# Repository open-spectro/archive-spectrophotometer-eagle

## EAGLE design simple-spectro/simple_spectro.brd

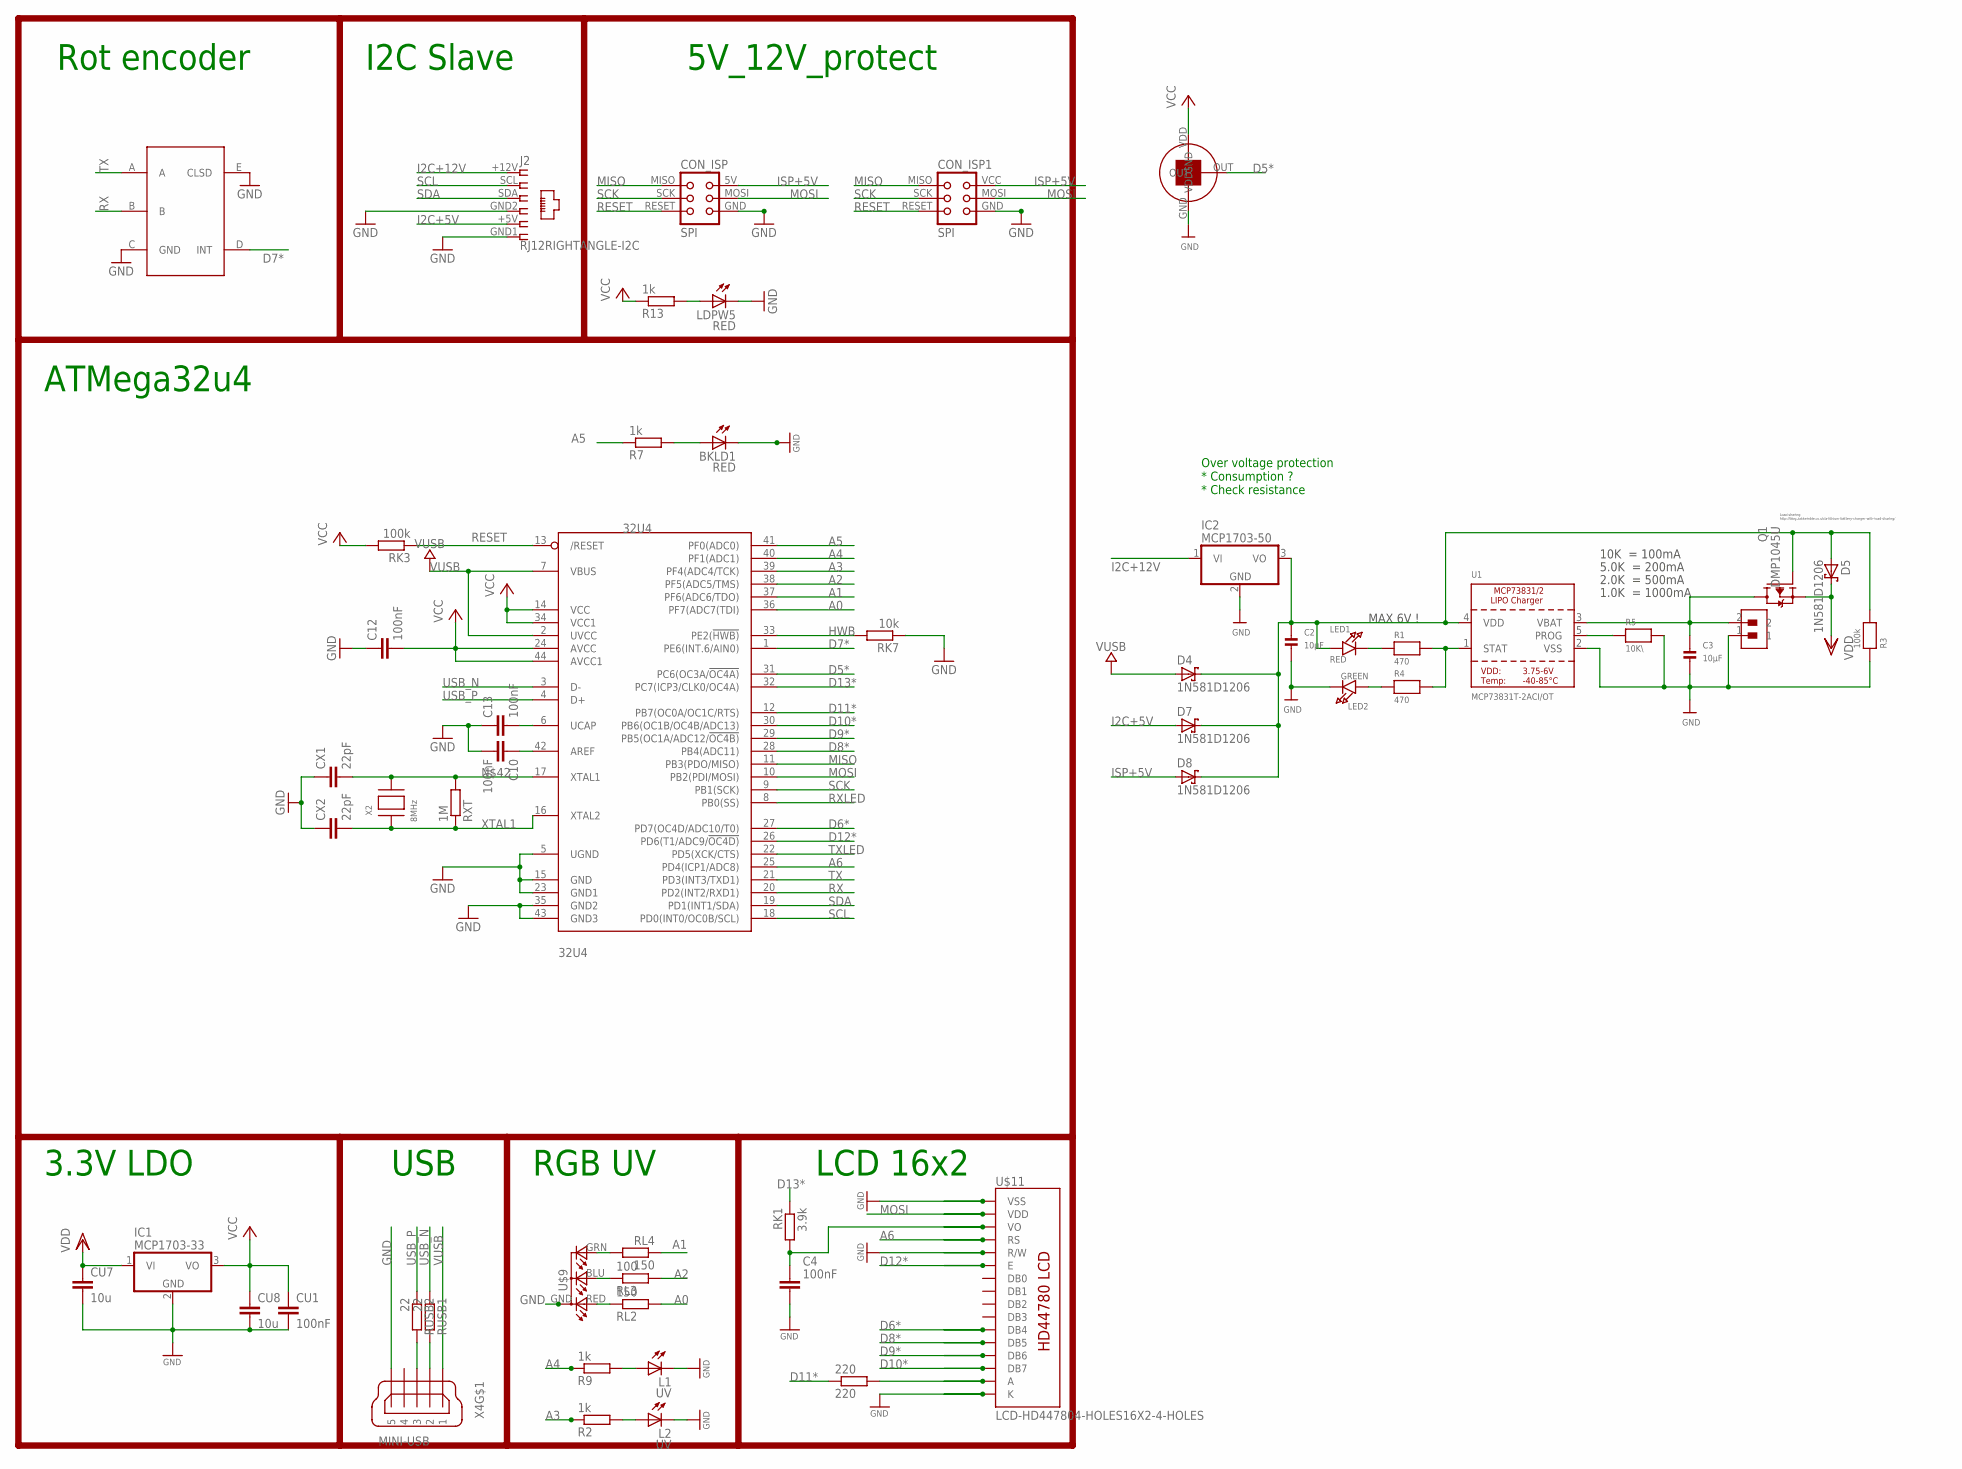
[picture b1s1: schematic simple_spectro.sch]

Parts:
32U4: 32U4; TQFP44
220: 220; R0805
BKLD1: RED; CHIP-LED0805
C2, C3: 10µF; 0805
C4: 100nF; C805
C10, C12, C13: 100nF; C1206
CON_ISP: SPI; TC2030-MCP-NL
CON_ISP1: SPI; TINYISP
CU1: 100nF; C0805
CU7, CU8: 10u; C0805
CX1, CX2: 22pF; C1206
D4, D5, D7, D8: 1N581D1206; LED-1206
IC1: MCP1703-33; SOT223
IC2: MCP1703-50; SOT223
J2: RJ12RIGHTANGLE-I2C; RJ12-RIGHTANGLE-I2C
L1: UV; LED5MM
L2: UV; LED3MM
LDPW5: RED; CHIP-LED0805
LED1: RED; CHIPLED_0805
LED2: GREEN; CHIPLED_0805
Q1: DMP1045U; SOT-23
R1, R4: 470; 0805
R2, R7, R9, R13: 1k; R0805
R3: 100k; 0805
R5: 10K\; 0805
RK1: 3.9k; R0805
RK3: 100k; M0805
RK7: 10k; M0805
RL2, RL4: 150; R0805
RL3: 100; R0805
RUSB1, RUSB2: 22; M1206
RXT: 1M; R0805
U1: MCP73831T-2ACI/OT; SOT23-5
U$1: EC11E
U$7: TSL237
U$9: RGB-COMMON-CATHODE; LED-TRICOLOR-THROUGHHOLE
U$11: LCD-HD447804-HOLES16X2-4-HOLES; LCD-16X2-4HOLES
U$12: CONN2; JST-2-XH
X2: 8MHz; NX6035
X4: MINI-USB; 32005-201

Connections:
A0: 32U4.36 (PF7(ADC7(TDI)), RL2.2
A1: 32U4.37 (PF6(ADC6/TDO)), RL4.1
A2: 32U4.38 (PF5(ADC5/TMS)), RL3.2
A3: 32U4.39 (PF4(ADC4/TCK)), R2.1
A4: 32U4.40 (PF1(ADC1)), R9.1
A5: 32U4.41 (PF0(ADC0)), R7.1
A6: 32U4.25 (PD4(ICP1/ADC8)), U$11.4 (RS)
AREF: 32U4.42 (AREF), C10.1
D5*: 32U4.31 (PC6(OC3A/!OC4A)), U$7.OUT
D6*: 32U4.27 (PD7(OC4D/ADC10/T0)), U$11.11 (DB4)
D7*: 32U4.1 (PE6(INT.6/AIN0)), U$1.D (INT)
D8*: 32U4.28 (PB4(ADC11)), U$11.12 (DB5)
D9*: 32U4.29 (PB5(OC1A/ADC12/!OC4B)), U$11.13 (DB6)
D10*: 32U4.30 (PB6(OC1B/OC4B/ADC13)), U$11.14 (DB7)
D11*: 32U4.12 (PB7(OC0A/OC1C/RTS)), 220.1
D12*: 32U4.26 (PD6(T1/ADC9/!OC4D)), U$11.6 (E)
D13*: 32U4.32 (PC7(ICP3/CLK0/OC4A)), RK1.1
GND: 32U4.5 (UGND), 32U4.15 (GND), 32U4.23 (GND1), 32U4.35 (GND2), 32U4.43 (GND3), BKLD1.C, C2.2, C3.2, C4.2, C10.2, C12.1, C13.1, CON_ISP.GND, CON_ISP1.GND, CU1.2, CU7.2, CU8.2, CX1.1, CX2.1, IC1.2 (GND), IC2.2 (GND), J2.GND1 (6), J2.GND2 (4), L1.K (C), L2.K (C), LDPW5.C, LED2.C, R3.1, R5.2, RK7.1, U1.2 (VSS), U$1.C (GND), U$1.E (CLSD), U$7.GND, U$9.GND (A2), U$11.1 (VSS), U$11.5 (R/W), U$11.16 (K), U$12.1, X4.5
HWB: 32U4.33 (PE2(!HWB)), RK7.2
I2C+5V: D7.A, J2.+5V (5)
I2C+12V: IC2.1 (VI), J2.+12V (1)
ISP+5V: CON_ISP.5V (VCC), CON_ISP1.VCC, D8.A
MISO: 32U4.11 (PB3(PDO/MISO)), CON_ISP.MISO, CON_ISP1.MISO
MOSI: 32U4.10 (PB2(PDI/MOSI)), CON_ISP.MOSI, CON_ISP1.MOSI, U$11.2 (VDD)
unnamed: 32U4.6 (UCAP), C13.2
unnamed: C4.1, RK1.2, U$11.3 (VO)
unnamed: L1.A, R9.2
unnamed: LED1.C, R1.1
unnamed: R1.2, R4.2, U1.1 (STAT)
unnamed: R5.1, U1.5 (PROG)
unnamed: LED2.A, R4.1
unnamed: L2.A, R2.2
unnamed: RL4.2, U$9.GRN (CGREEN)
unnamed: RL3.1, U$9.BLU (CBLUE)
unnamed: 220.2, U$11.15 (A)
unnamed: LDPW5.A, R13.2
unnamed: RL2.1, U$9.RED (CRED)
unnamed: BKLD1.A, R7.2
unnamed: C2.1, D4.C, D5.A, D7.C, D8.C, IC2.3 (VO), LED1.A, Q1.1 (G), R3.2, U1.4 (VDD)
unnamed: 32U4.17 (XTAL1), CX1.2, RXT.2, X2.P$2
RESET: 32U4.13 (/RESET), CON_ISP.RESET, CON_ISP1.RESET, RK3.1
RX: 32U4.20 (PD2(INT2/RXD1)), U$1.B
RXLED: 32U4.8 (PB0(SS))
SCK: 32U4.9 (PB1(SCK)), CON_ISP.SCK, CON_ISP1.SCK
SCL: 32U4.18 (PD0(INT0/OC0B/SCL)), J2.SCL (2)
SDA: 32U4.19 (PD1(INT1/SDA)), J2.SDA (3)
TX: 32U4.21 (PD3(INT3/TXD1)), U$1.A
TXLED: 32U4.22 (PD5(XCK/CTS))
USBC_N: RUSB1.2, X4.2
USBC_P: RUSB2.2, X4.3
USB_N: 32U4.3 (D-), RUSB1.1
USB_P: 32U4.4 (D+), RUSB2.1
VBAT1: C3.1, Q1.3 (D), U1.3 (VBAT), U$12.2
VCC: 32U4.14 (VCC), 32U4.24 (AVCC), 32U4.34 (VCC1), 32U4.44 (AVCC1), C12.2, CU1.1, CU8.1, IC1.3 (VO), R13.1, RK3.2, U$7.VDD
VDD: CU7.1, D5.C, IC1.1 (VI), Q1.2 (S)
VUSB: 32U4.2 (UVCC), 32U4.7 (VBUS), D4.A, X4.1
XTAL1: 32U4.16 (XTAL2), CX2.2, RXT.1, X2.P$1

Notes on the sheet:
USB
5V_12V_protect
ATMega32u4
I2C Slave
LCD 16x2
Rot encoder
3.3V LDO
10K = 100mA
5.0K = 200mA
2.0K = 500mA
1.0K = 1000mA
MAX 6V !
Load sharing: http://blog.zakkemble.co.uk/a-lithium-battery-charger-with-load-sharing/
RGB UV
Over voltage protection * Consumption ? * Check resistance

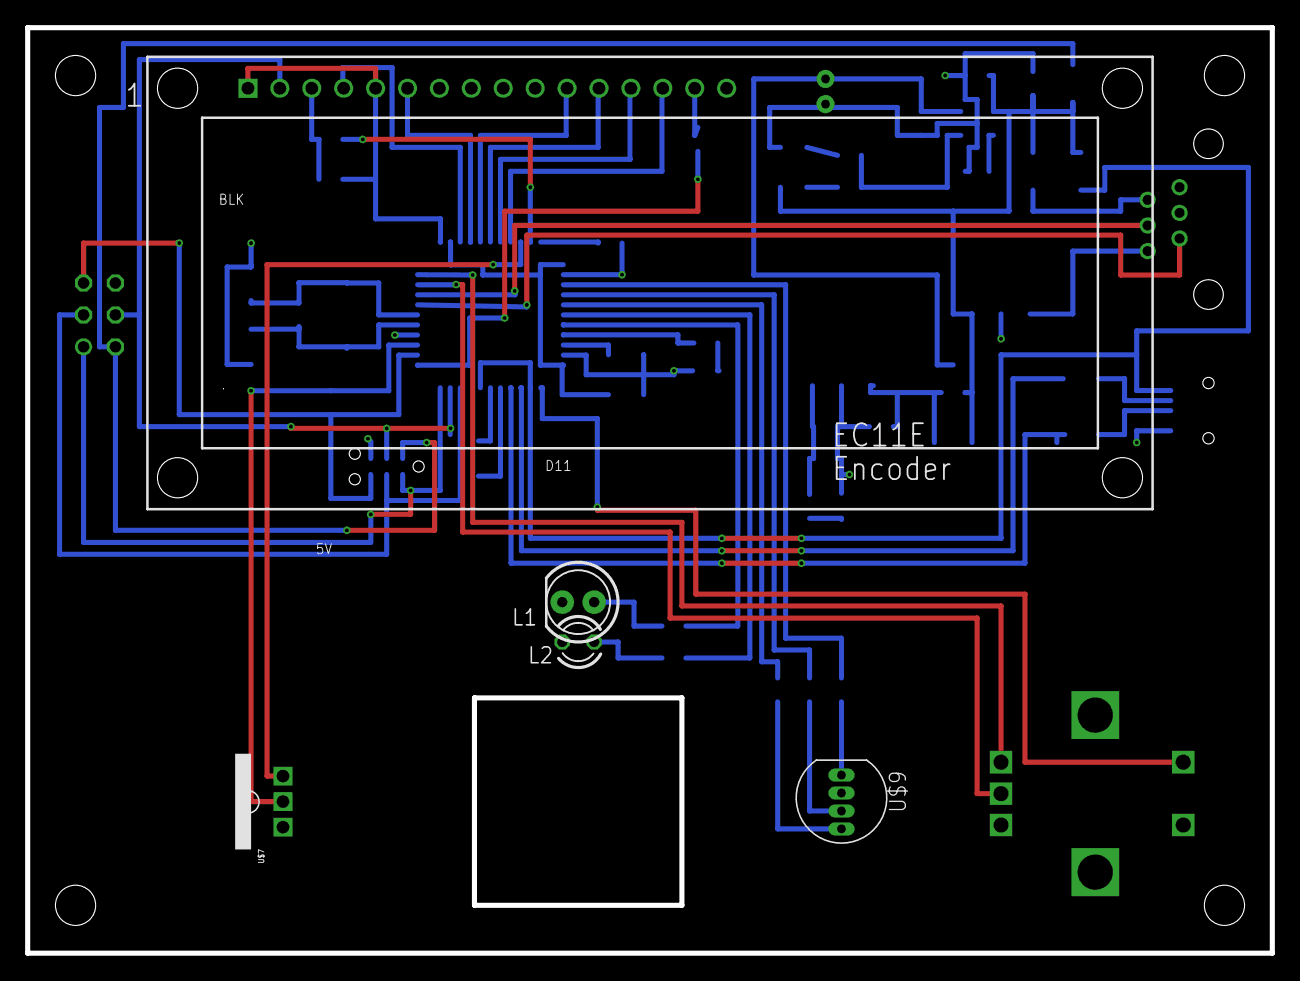
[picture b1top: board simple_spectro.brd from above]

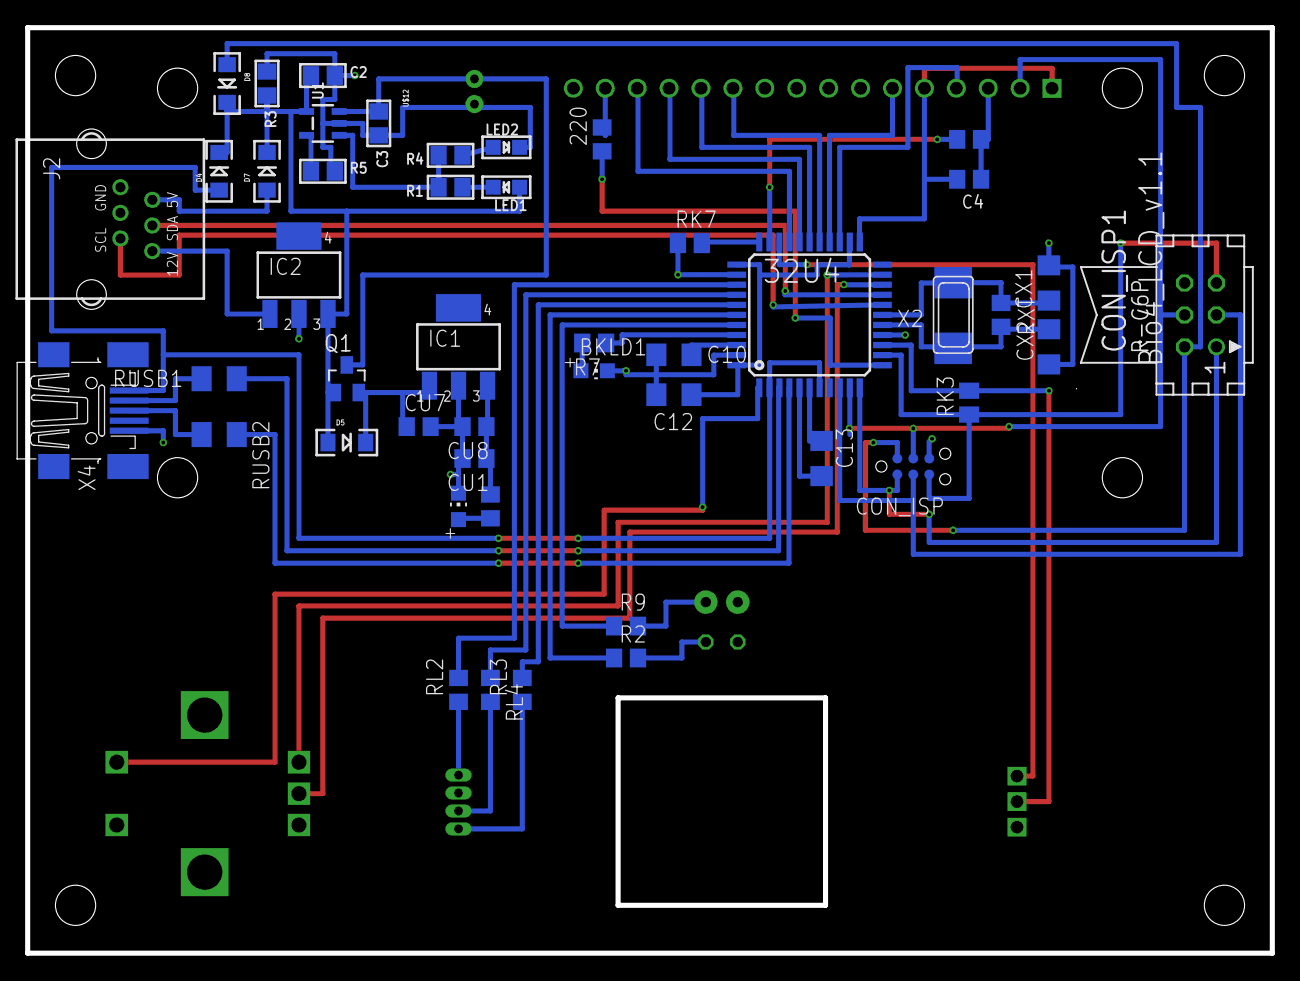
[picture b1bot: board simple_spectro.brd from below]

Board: 4 copper layers, 99.1 x 73.7 mm, 54 parts (48 on the bottom side), 55 nets.

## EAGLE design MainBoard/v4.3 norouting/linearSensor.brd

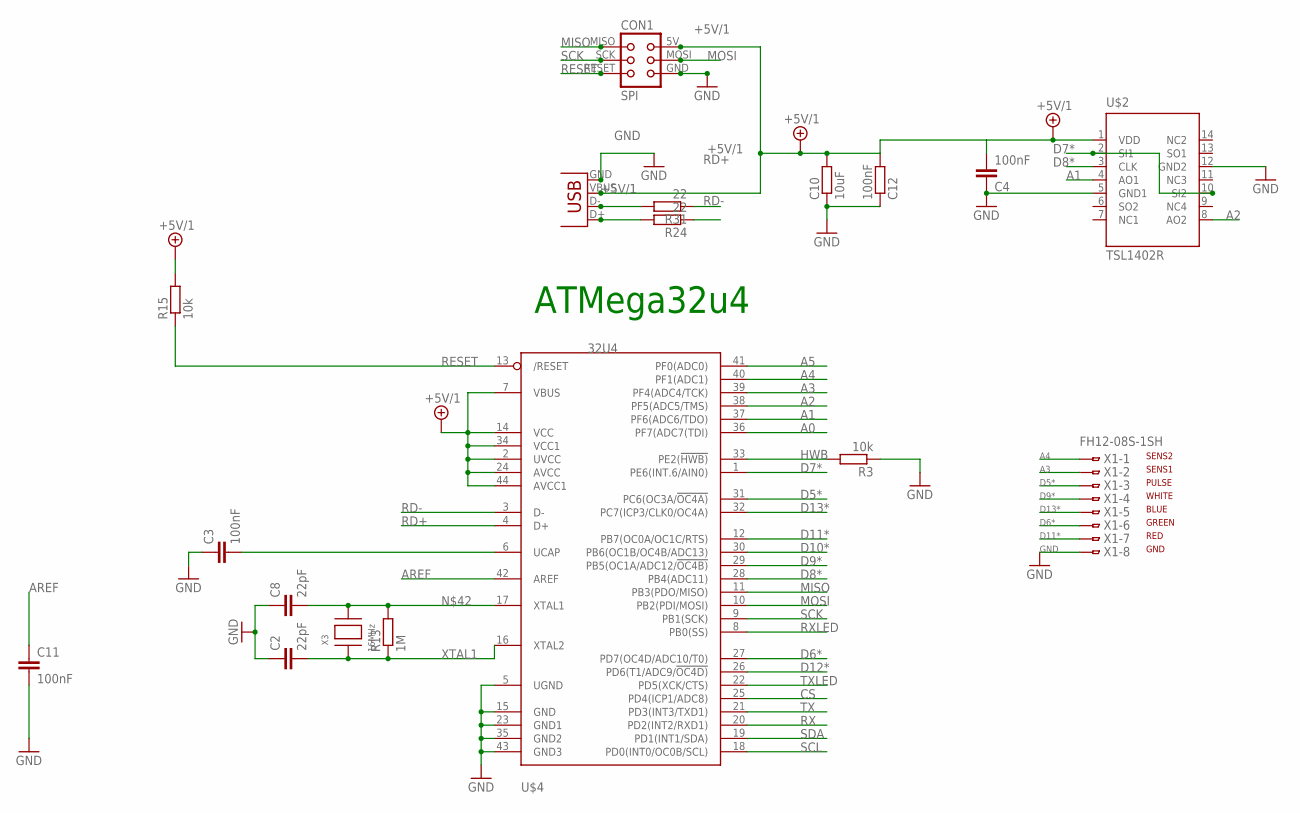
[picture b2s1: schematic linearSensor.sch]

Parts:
C2, C8: 22pF; C0805K
C3, C11: 100nF; C0805K
C4: 100nF; C0805
C10: 10uF; M0805
C12: 100nF; M0805
CON1: SPI; TC2030-MCP-NL
R3, R15: 10k; M0805
R13: 1M; M0805
R24, R31: 22; M0805
U$2: TSL1402R; DIL14
U$4: 32U4; TQFP44
X1: FH12-08S-1SH
X2: USB-MICROB
X3: 16MHz; NX6035

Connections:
+5V/1: C4.2, C10.2, C12.2, CON1.5V (VCC), R15.2, U$2.1 (VDD), U$4.2 (UVCC), U$4.7 (VBUS), U$4.14 (VCC), U$4.24 (AVCC), U$4.34 (VCC1), U$4.44 (AVCC1), X2.VBUS
A0: U$4.36 (PF7(ADC7(TDI))
A1: U$2.4 (AO1), U$4.37 (PF6(ADC6/TDO))
A2: U$2.8 (AO2), U$4.38 (PF5(ADC5/TMS))
A3: U$4.39 (PF4(ADC4/TCK)), X1.2
A4: U$4.40 (PF1(ADC1)), X1.1
A5: U$4.41 (PF0(ADC0))
AREF: C11.1, U$4.42 (AREF)
CS: U$4.25 (PD4(ICP1/ADC8))
D5*: U$4.31 (PC6(OC3A/!OC4A)), X1.3
D6*: U$4.27 (PD7(OC4D/ADC10/T0)), X1.6
D7*: U$2.2 (SI1), U$2.10 (SI2), U$4.1 (PE6(INT.6/AIN0))
D8*: U$2.3 (CLK), U$4.28 (PB4(ADC11))
D9*: U$4.29 (PB5(OC1A/ADC12/!OC4B)), X1.4
D10*: U$4.30 (PB6(OC1B/OC4B/ADC13))
D11*: U$4.12 (PB7(OC0A/OC1C/RTS)), X1.7
D12*: U$4.26 (PD6(T1/ADC9/!OC4D))
D13*: U$4.32 (PC7(ICP3/CLK0/OC4A)), X1.5
D_USB+: R24.2, X2.D+
D_USB-: R31.2, X2.D-
GND: C2.1, C3.1, C4.1, C8.1, C10.1, C11.2, C12.1, CON1.GND, R3.1, U$2.5 (GND1), U$2.12 (GND2), U$4.5 (UGND), U$4.15 (GND), U$4.23 (GND1), U$4.35 (GND2), U$4.43 (GND3), X1.8, X2.GND
HWB: R3.2, U$4.33 (PE2(!HWB))
MISO: CON1.MISO, U$4.11 (PB3(PDO/MISO))
MOSI: CON1.MOSI, U$4.10 (PB2(PDI/MOSI))
unnamed: C3.2, U$4.6 (UCAP)
unnamed: C8.2, R13.2, U$4.17 (XTAL1), X3.P$2
RD+: R24.1, U$4.4 (D+)
RD-: R31.1, U$4.3 (D-)
RESET: CON1.RESET, R15.1, U$4.13 (/RESET)
RX: U$4.20 (PD2(INT2/RXD1))
RXLED: U$4.8 (PB0(SS))
SCK: CON1.SCK, U$4.9 (PB1(SCK))
SCL: U$4.18 (PD0(INT0/OC0B/SCL))
SDA: U$4.19 (PD1(INT1/SDA))
TX: U$4.21 (PD3(INT3/TXD1))
TXLED: U$4.22 (PD5(XCK/CTS))
XTAL1: C2.2, R13.1, U$4.16 (XTAL2), X3.P$1

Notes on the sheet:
ATMega32u4
GND
RED
GREEN
BLUE
WHITE
PULSE
SENS1
SENS2

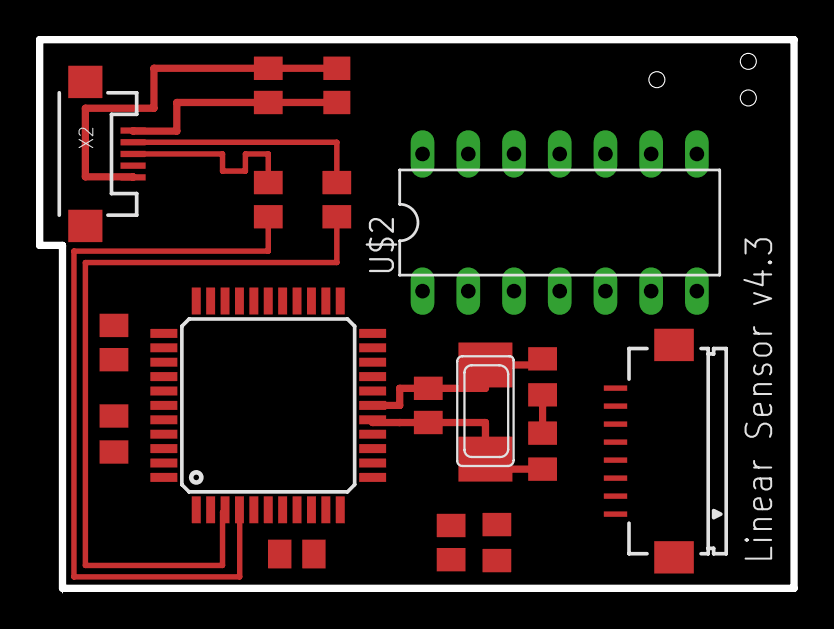
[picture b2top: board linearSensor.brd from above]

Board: 2 copper layers, 41.9 x 30.5 mm, 18 parts (1 on the bottom side), 26 nets.

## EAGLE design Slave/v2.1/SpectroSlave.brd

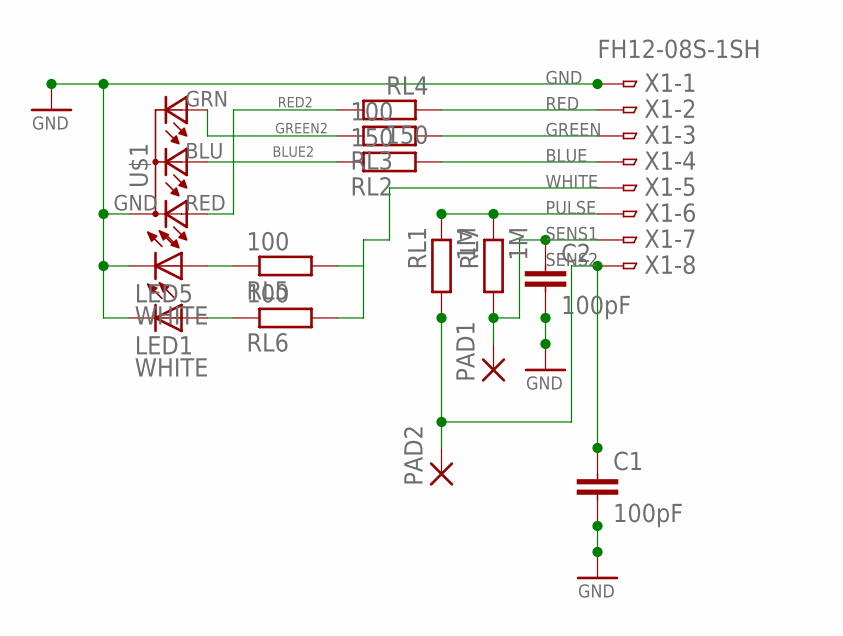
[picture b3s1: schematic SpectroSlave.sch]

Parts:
C1, C2: 100pF; C0805
LED1, LED5: WHITE; LED3MM
PAD1, PAD2: SMD5; SMD2,54-5,08
RL1, RL7: 1M; R0805
RL2, RL4: 150; R0805
RL3, RL5, RL6: 100; R0805
U$1: RGB-COMMON-CATHODE; LED-TRICOLOR-THROUGHHOLE
X1: FH12-08S-1SH

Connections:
BLUE: RL2.2, X1.4
BLUE2: RL2.1, U$1.BLU (CBLUE)
GND: C1.2, C2.2, LED1.K (C), LED5.K (C), U$1.GND (A2), X1.1
GREEN: RL3.2, X1.3
GREEN2: RL3.1, U$1.GRN (CGREEN)
unnamed: LED5.A, RL5.1
unnamed: LED1.A, RL6.1
PULSE: RL1.1, RL7.1, X1.6
RED: RL4.1, X1.2
RED2: RL4.2, U$1.RED (CRED)
SENS1: C2.1, PAD1.1, RL7.2, X1.7
SENS2: C1.1, PAD2.1, RL1.2, X1.8
WHITE: RL5.2, RL6.2, X1.5

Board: 2 copper layers, 15 parts (2 on the bottom side), 13 nets, no tracks yet.

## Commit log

2015-08-18 First release after split
2015-09-01 Remove arduino files
2015-10-13 Add new version with fix
2015-12-27 Add new corrected version
2017-05-21 Add simple spectro and odcs
2017-05-25 starting disposition of components in simple spectro
2017-05-25 Add gitignore
2017-05-25 Update simple spectro
2017-05-28 Start routing
2017-05-29 work in progress
2017-06-02 removed useless D6 schottky
2017-06-05 first version of simple spectro
2017-06-10 Close to final
2017-06-10 Final v1 version
2017-06-10 add gerber
2017-07-07 work on v1.0.1
2017-07-08 Move project to spectrophotometer

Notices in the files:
parts and their libraries:
lpatiny: ©2009 ROFA.cz - modified and updated by Robert Darlington ‹rdarlington@gmail.com›
SparkFun: Licensing: CC v3.0 Share-Alike You are welcome to use this library for commercial purposes.
